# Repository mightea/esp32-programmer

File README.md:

# esp32-programmer

<p style="background-color:yellow">
<font color="black"> ⚠️  Work in progress...</font>
</p>

Serial programmer for ESP32 and ESP8266 boards designed with [KiCad EDA](https://www.kicad.org/).
The programmer has the following features:

- TC2030-IDC connector
- USB-C connector
- 3.3v Power Switch (for connecting to serial console with external board power)
- Onboard RX/TX status LED's

## Project Status

- [ ] Design basic PCB layout
- [ ] Generate fabrication data
- [ ] Fabicate prototypes
- [ ] Test prototype

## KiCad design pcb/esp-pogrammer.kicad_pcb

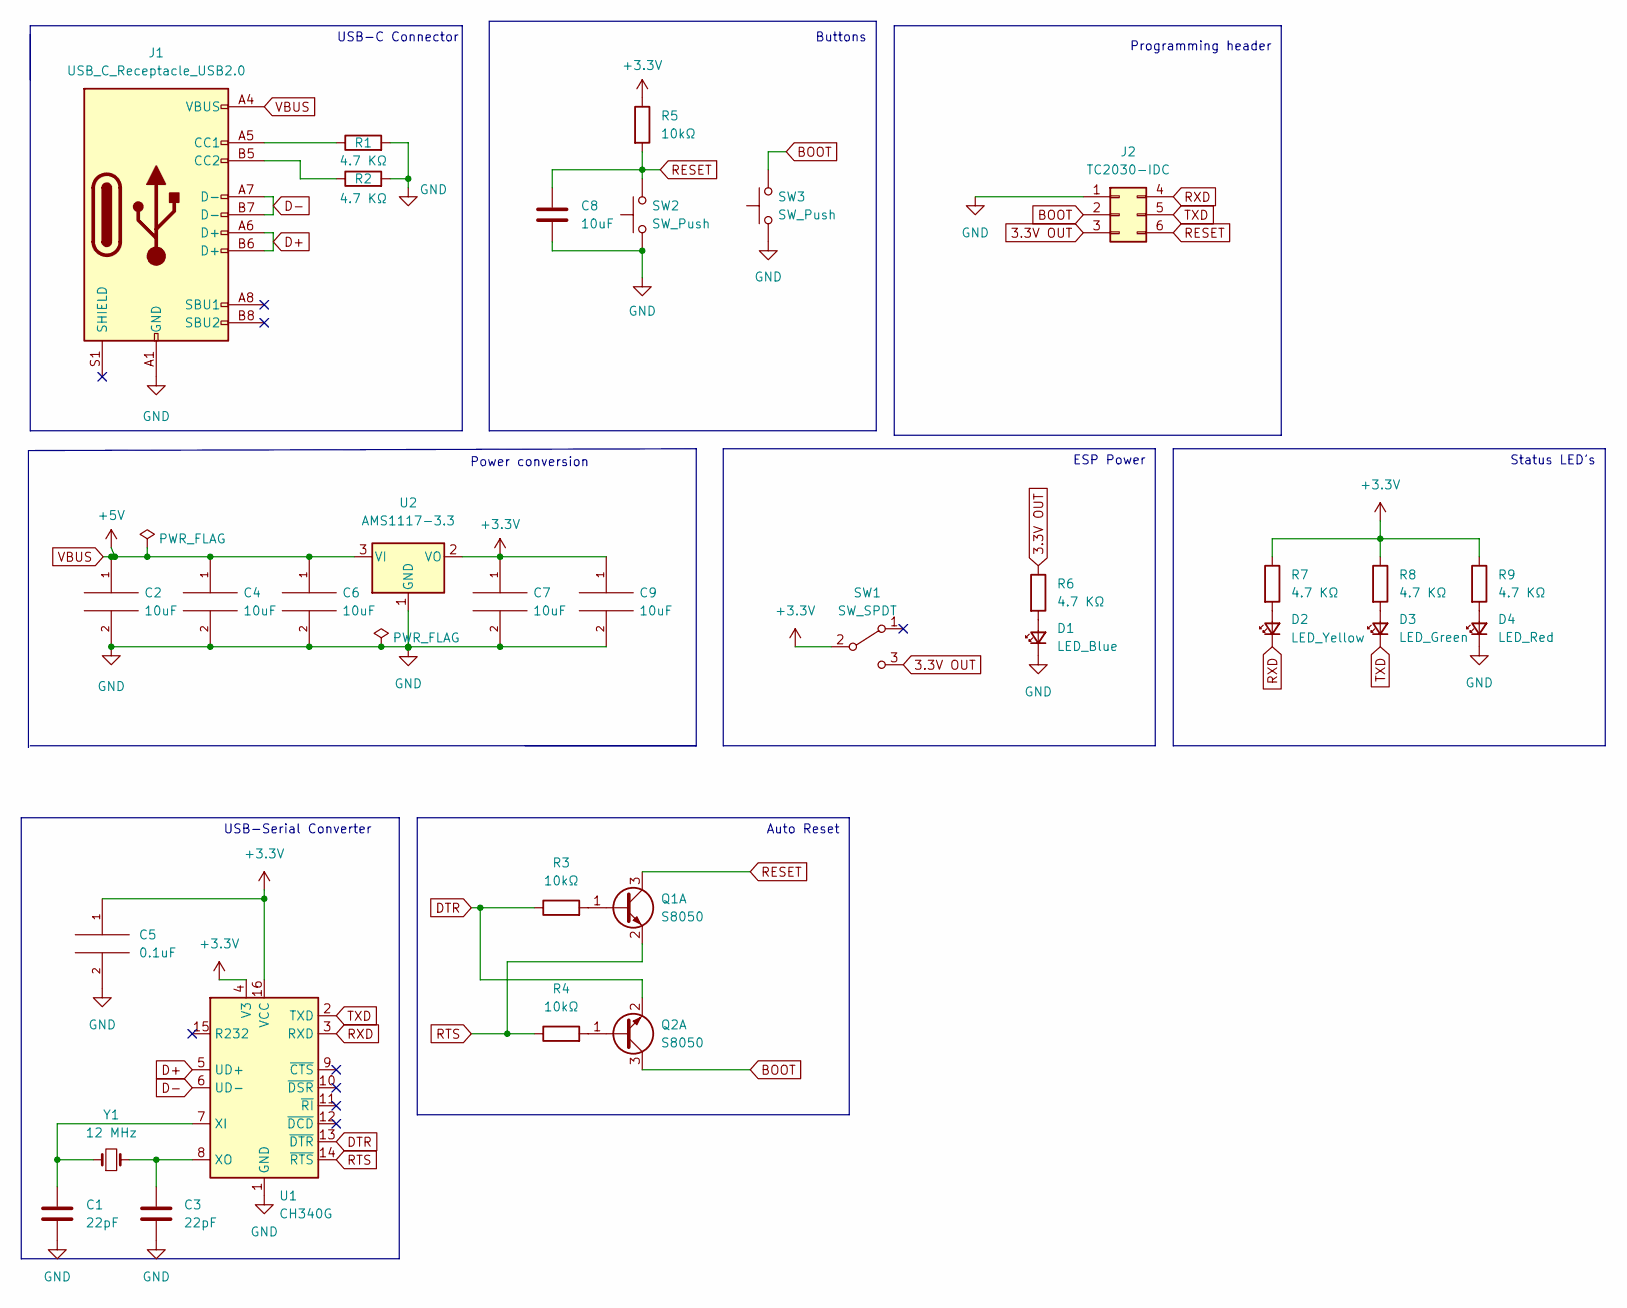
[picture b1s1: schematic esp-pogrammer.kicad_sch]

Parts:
C1, C3: 22pF; C_0603_1608Metric
C2, C4, C6, C7, C8, C9: 10uF; C_0603_1608Metric
C5: 0.1uF; C_0603_1608Metric
D1: LED_Blue; LED_0603_1608Metric
D2: LED_Yellow; LED_0603_1608Metric
D3: LED_Green; LED_0603_1608Metric
D4: LED_Red; LED_0603_1608Metric
J1: USB_C_Receptacle_USB2.0; USB_C_Receptacle_HRO_TYPE-C-31-M-12
J2: TC2030-IDC; IDC-Header_2x03_P2.54mm_Vertical
Q1, Q2: S8050; SOT-23
R1, R2: 4.7 KΩ; R_0603_1608Metric
R3, R4, R5: 10kΩ; R_0603_1608Metric
R6, R7, R8, R9: 4.7 KΩ; R_0603_1608Metric; jlcpcb C25905
SW1: SW_SPDT; SW_CuK_JS202011AQN_DPDT_Angled
SW2, SW3: SW_Push; TS-1187A-B-A-B
U1: CH340G; SOIC-16_3.9x9.9mm_P1.27mm
U2: AMS1117-3.3; SOT-223-3_TabPin2
Y1: 12 MHz; Crystal_SMD_0603-2Pin_6.0x3.5mm

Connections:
3.3V OUT: J2.3, R6.1, SW1.3 (C)
+3V3: C5.1, C7.1, C9.1, R5.1, R7.1, R8.1, R9.1, SW1.2 (B), U1.4 (V3), U1.16 (VCC), U2.2 (VO)
BOOT: J2.2, Q2.3 (C3), SW3.2
D+: J1.A6 (D+), J1.B6 (D+), U1.5 (UD+)
D-: J1.A7 (D-), J1.B7 (D-), U1.6 (UD-)
DTR: Q2.2 (E2), R3.1, U1.13 (~DTR)
GND: C1.2, C2.2, C3.2, C4.2, C5.2, C6.2, C7.2, C8.2, C9.2, D1.1 (K), D4.1 (K), J1.A1 (GND), J1.A12 (GND), J1.B1 (GND), J1.B12 (GND), J2.1, R1.2, R2.2, SW2.1, SW3.1, U1.1 (GND), U2.1 (GND)
unnamed: C1.1, U1.7 (XI), Y1.1
unnamed: C3.1, U1.8 (XO), Y1.2
unnamed: D1.2 (A), R6.2
unnamed: D2.2 (A), R7.2
unnamed: D3.2 (A), R8.2
unnamed: D4.2 (A), R9.2
unnamed: J1.A5 (CC1), R1.1
unnamed: J1.B5 (CC2), R2.1
unnamed: Q1.1 (B1), R3.2
unnamed: Q2.1 (B1), R4.2
RESET: C8.1, J2.6, Q1.3 (C3), R5.2, SW2.2
RTS: Q1.2 (E2), R4.1, U1.14 (~RTS)
RXD: D2.1 (K), J2.4, U1.3 (RXD)
TXD: D3.1 (K), J2.5, U1.2 (TXD)
VBUS: C2.1, C4.1, C6.1, J1.A4 (VBUS), J1.A9 (VBUS), J1.B4 (VBUS), J1.B9 (VBUS), U2.3 (VI)

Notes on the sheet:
Status LED's
Programming header
Power conversion
Auto Reset
Buttons
USB-Serial Converter
USB-C Connector
ESP Power

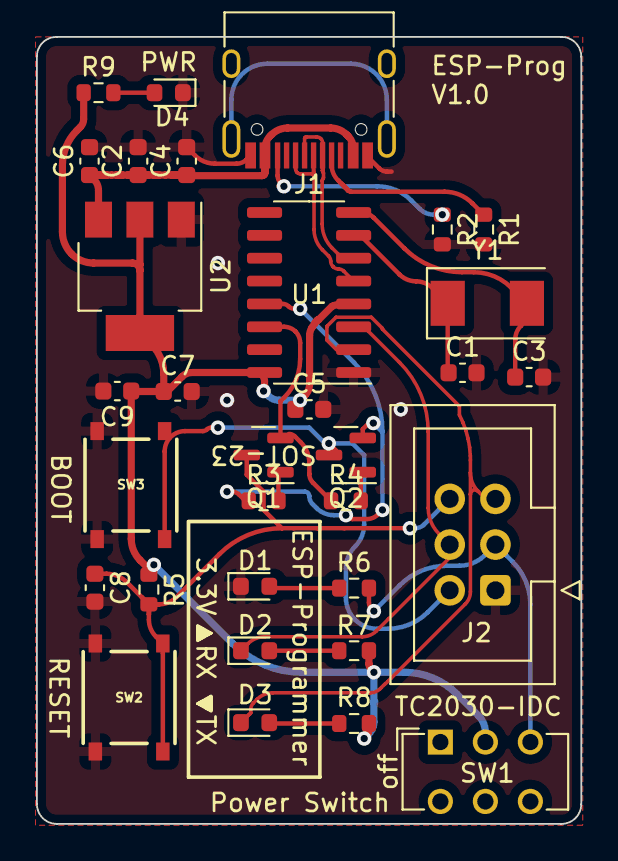
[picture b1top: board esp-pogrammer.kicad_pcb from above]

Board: 2 copper layers, 30.2 x 43.7 mm, 32 parts (0 on the bottom side), 22 nets.

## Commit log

2022-05-30 initial import
2022-05-31 updates layout
2022-05-31 added some filter caps, replaced local chip filter, replaced crystal caps, fixed switched power on reset, routed, rounded.
2022-06-04 fixed transistors. minor changes. ordered prototype 0.1.
